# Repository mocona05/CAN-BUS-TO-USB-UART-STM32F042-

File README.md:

# CAN-BUS-TO-USB-UART-STM32F042-
CAN-BUS TO USB-UART(STM32F042)
http://cafe.naver.com/hobbydyi/1781

lcd
http://ko.aliexpress.com/item/1-3-inch-White-OLED-Screen-SH1106-Drive-IC-128-64-I2C-SPI-Parallel-Interface/32299639218.html

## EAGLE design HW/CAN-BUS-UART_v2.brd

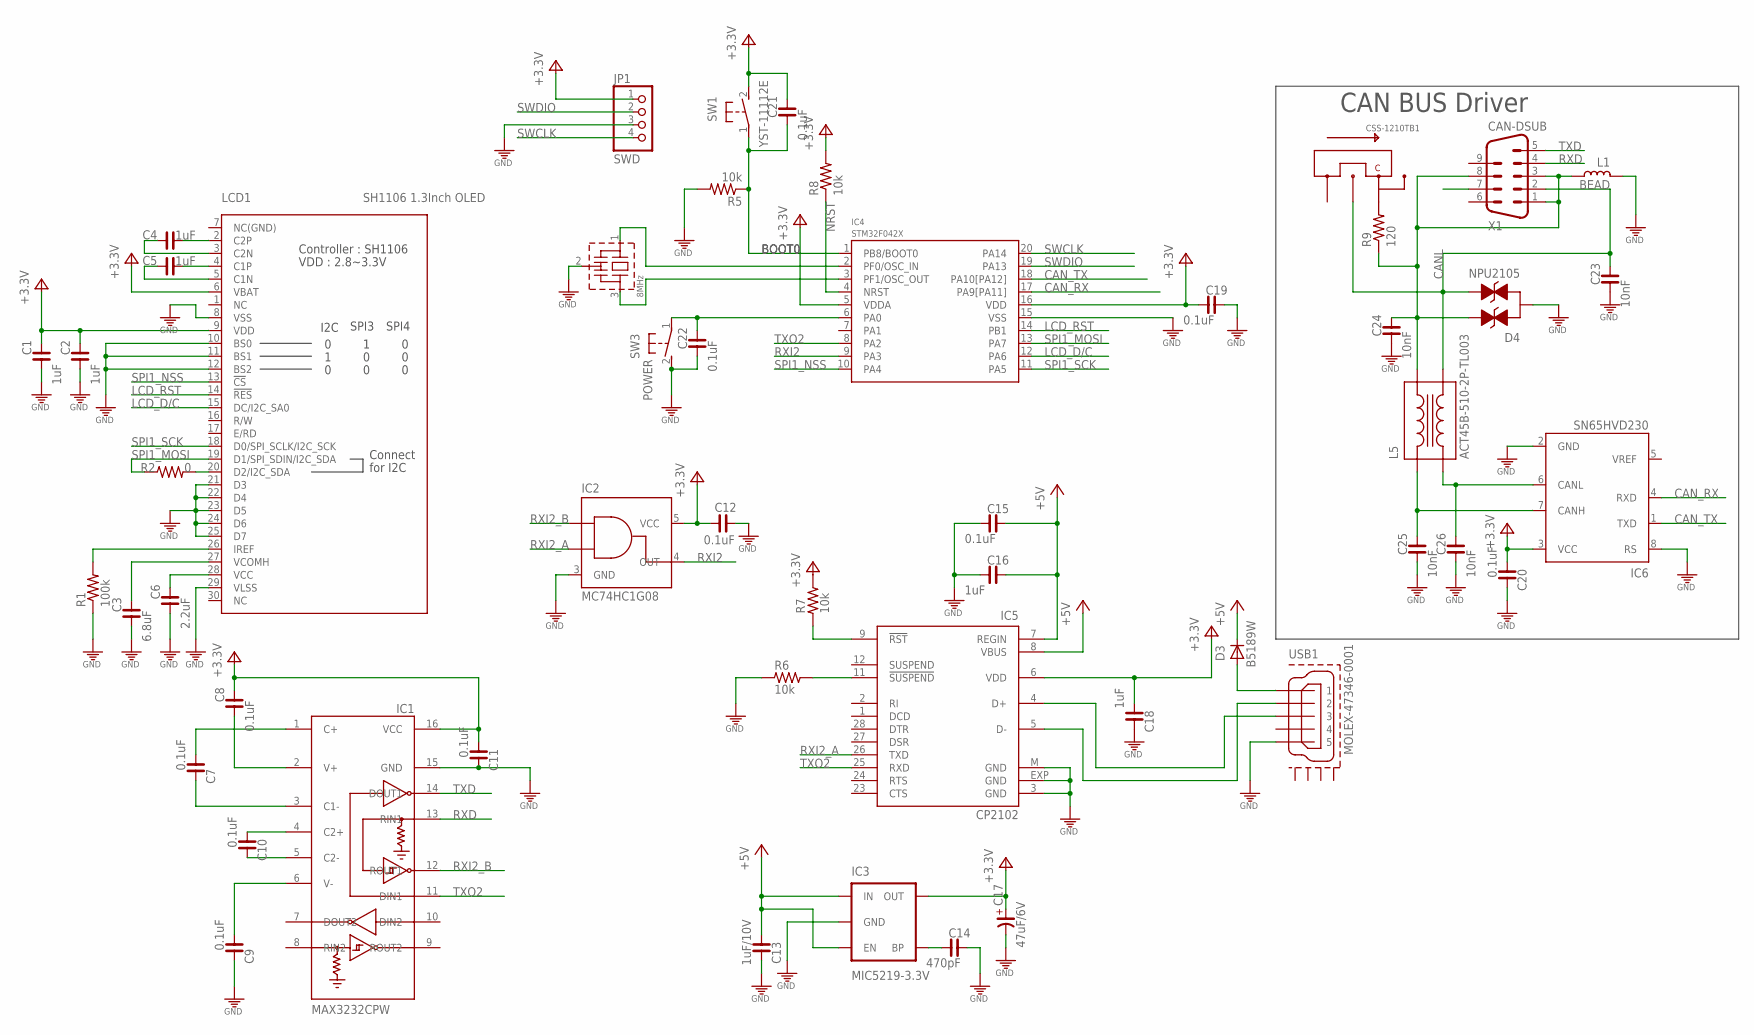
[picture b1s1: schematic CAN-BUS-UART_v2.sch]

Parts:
C1, C2, C4, C5, C16, C18: 1uF; C0603
C3: 6.8uF; C0805
C6: 2.2uF; C0805
C7, C8, C9, C10, C11, C12, C15, C19, C20, C21, C22: 0.1uF; C0603
C13: 1uF/10V; C0603
C14: 470pF; C0603
C17: 47uF/6V; C3528-21/T
C23, C24, C25, C26: 10nF; C0603
D3: B5189W; SOD323
D4: NPU2105; SOT23
IC1: MAX3232CPW; PW_R-PDSO-G16
IC2: MC74HC1G08; SOT23-5L_MC74HC1G08
IC3: MIC5219-3.3V; SOT23-5
IC4: STM32F042X; TSSOP20
IC5: CP2102; MLP28
IC6: SN65HVD230; SO8
JP1: SWD; 1X04M
L1: BEAD; L0805
L5: ACT45B-510-2P-TL003; ACT45B
LCD1: SH1106 1.3Inch OLED; SH1106_1.3OLED_BUTTOM
Q1: 8MHz; CSTLA_X
R1: 100k; R0603@1
R2: 0; R0603@1
R5, R8: 10k; R0603@1
R6, R7: 10k; R0603
R9: 120; R0603@1
SW1: YST-11112E; YST-1112E
SW2: CSS-1210TB1; CSS-1210TB
SW3: POWER; KLT-1105VE
USB1: MOLEX-47346-0001; MOLEX-47364-0001
X1: CAN-DSUB; M09H-1

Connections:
3V3: C1.1, C2.1, C8.1, C11.2, C12.2, C17.+, C18.2, C19.2, C20.2, C21.1, IC1.16 (VCC), IC2.5 (VCC), IC3.5 (OUT), IC4.5 (VDDA), IC4.16 (VDD), IC5.6 (VDD), IC6.3 (VCC), JP1.1, LCD1.6 (VBAT), LCD1.9 (VDD), R7.2, R8.2, SW1.2
+5V: C13.2, C15.1, C16.1, D3.C, IC3.1 (IN), IC3.3 (EN), IC5.7 (REGIN), IC5.8 (VBUS)
BOOT0: C21.2, IC4.1 (PB8/BOOT0), R5.1, SW1.1
CANL: C23.1, D4.S (PIN2), L5.3, SW2.2, X1.2
CAN_RX: IC4.17 (PA9[PA11]), IC6.4 (RXD)
CAN_TX: IC4.18 (PA10[PA12]), IC6.1 (TXD)
GND: C1.2, C2.2, C3.2, C6.2, C9.1, C11.1, C12.1, C13.1, C14.1, C15.2, C16.2, C17.-, C18.1, C19.1, C20.1, C22.2, C23.2, C24.2, C25.2, C26.2, D4.D (PIN3), IC1.15 (GND), IC2.3 (GND), IC3.2 (GND), IC4.15 (VSS), IC5.3 (GND), IC5.EXP (GND), IC5.M (GND), IC6.2 (GND), IC6.8 (RS), JP1.3, L1.2, LCD1.8 (VSS), LCD1.10 (BS0), LCD1.11 (BS1), LCD1.12 (BS2), LCD1.21 (D3), LCD1.22 (D4), LCD1.23 (D5), LCD1.24 (D6), LCD1.25 (D7), LCD1.29 (VLSS), Q1.2 (GND), R1.1, R5.2, R6.1, SW3.2, USB1.5
LCD_D/C: IC4.12 (PA6), LCD1.15 (DC/I2C_SA0)
LCD_RST: IC4.14 (PB1), LCD1.14 (!RES)
unnamed: IC5.9 (!RST), R7.1
unnamed: IC4.2 (PF0/OSC_IN), Q1.1 (IN)
unnamed: IC4.3 (PF1/OSC_OUT), Q1.3 (OUT)
unnamed: D3.A, USB1.1
unnamed: R9.2, SW2.3
unnamed: LCD1.26 (IREF), R1.2
unnamed: C22.1, IC4.6 (PA0), SW3.1
unnamed: IC5.5 (D-), USB1.2
unnamed: C24.1, D4.G (PIN1), L1.1, L5.4, R9.1, X1.1, X1.3, X1.8
unnamed: C14.2, IC3.4 (BP)
unnamed: C26.1, IC6.6 (CANL), L5.2
unnamed: C10.1, IC1.5 (C2-)
unnamed: C4.2, LCD1.2 (C2P)
unnamed: C4.1, LCD1.3 (C2N)
unnamed: C5.2, LCD1.4 (C1P)
unnamed: C5.1, LCD1.5 (C1N)
unnamed: LCD1.20 (D2/I2C_SDA), R2.2
unnamed: IC5.4 (D+), USB1.3
unnamed: C3.1, LCD1.27 (VCOMH)
unnamed: C6.1, LCD1.28 (VCC)
unnamed: IC5.11 (!SUSPEND), R6.2
unnamed: C25.1, IC6.7 (CANH), L5.1
unnamed: C10.2, IC1.4 (C2+)
unnamed: C9.2, IC1.6 (V-)
unnamed: C7.2, IC1.1 (C+)
unnamed: C7.1, IC1.3 (C1-)
unnamed: C8.2, IC1.2 (V+)
NRST: IC4.4 (NRST), R8.1
RXD: IC1.13 (RIN1), X1.4
RXI2: IC2.4 (OUT), IC4.9 (PA3)
RXI2_A: IC2.2 (INA), IC5.26 (TXD)
RXI2_B: IC1.12 (ROUT1), IC2.1 (INB)
SPI1_MOSI: IC4.13 (PA7), LCD1.19 (D1/SPI_SDIN/I2C_SDA), R2.1
SPI1_NSS: IC4.10 (PA4), LCD1.13 (!CS)
SPI1_SCK: IC4.11 (PA5), LCD1.18 (D0/SPI_SCLK/I2C_SCK)
SWCLK: IC4.20 (PA14), JP1.4
SWDIO: IC4.19 (PA13), JP1.2
TXD: IC1.14 (DOUT1), X1.5
TXO2: IC1.11 (DIN1), IC4.8 (PA2), IC5.25 (RXD)

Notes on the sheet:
CAN BUS Driver

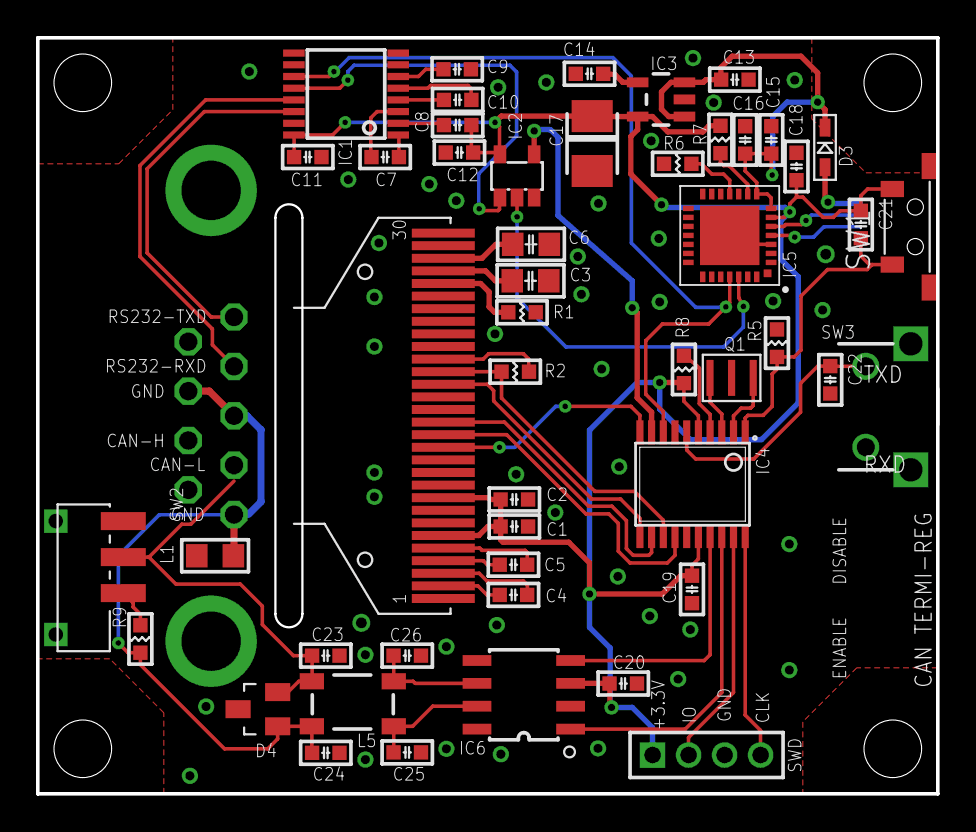
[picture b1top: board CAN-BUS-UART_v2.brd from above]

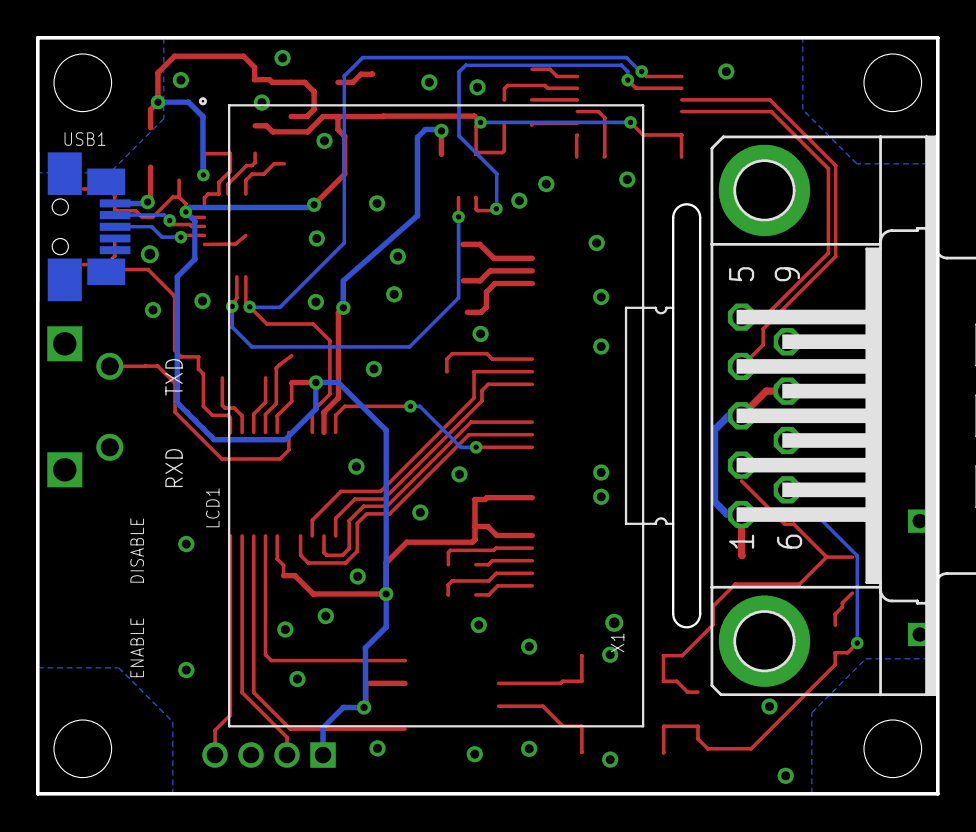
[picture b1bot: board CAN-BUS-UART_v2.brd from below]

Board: 2 copper layers, 50.0 x 42.0 mm, 51 parts (2 on the bottom side), 48 nets.

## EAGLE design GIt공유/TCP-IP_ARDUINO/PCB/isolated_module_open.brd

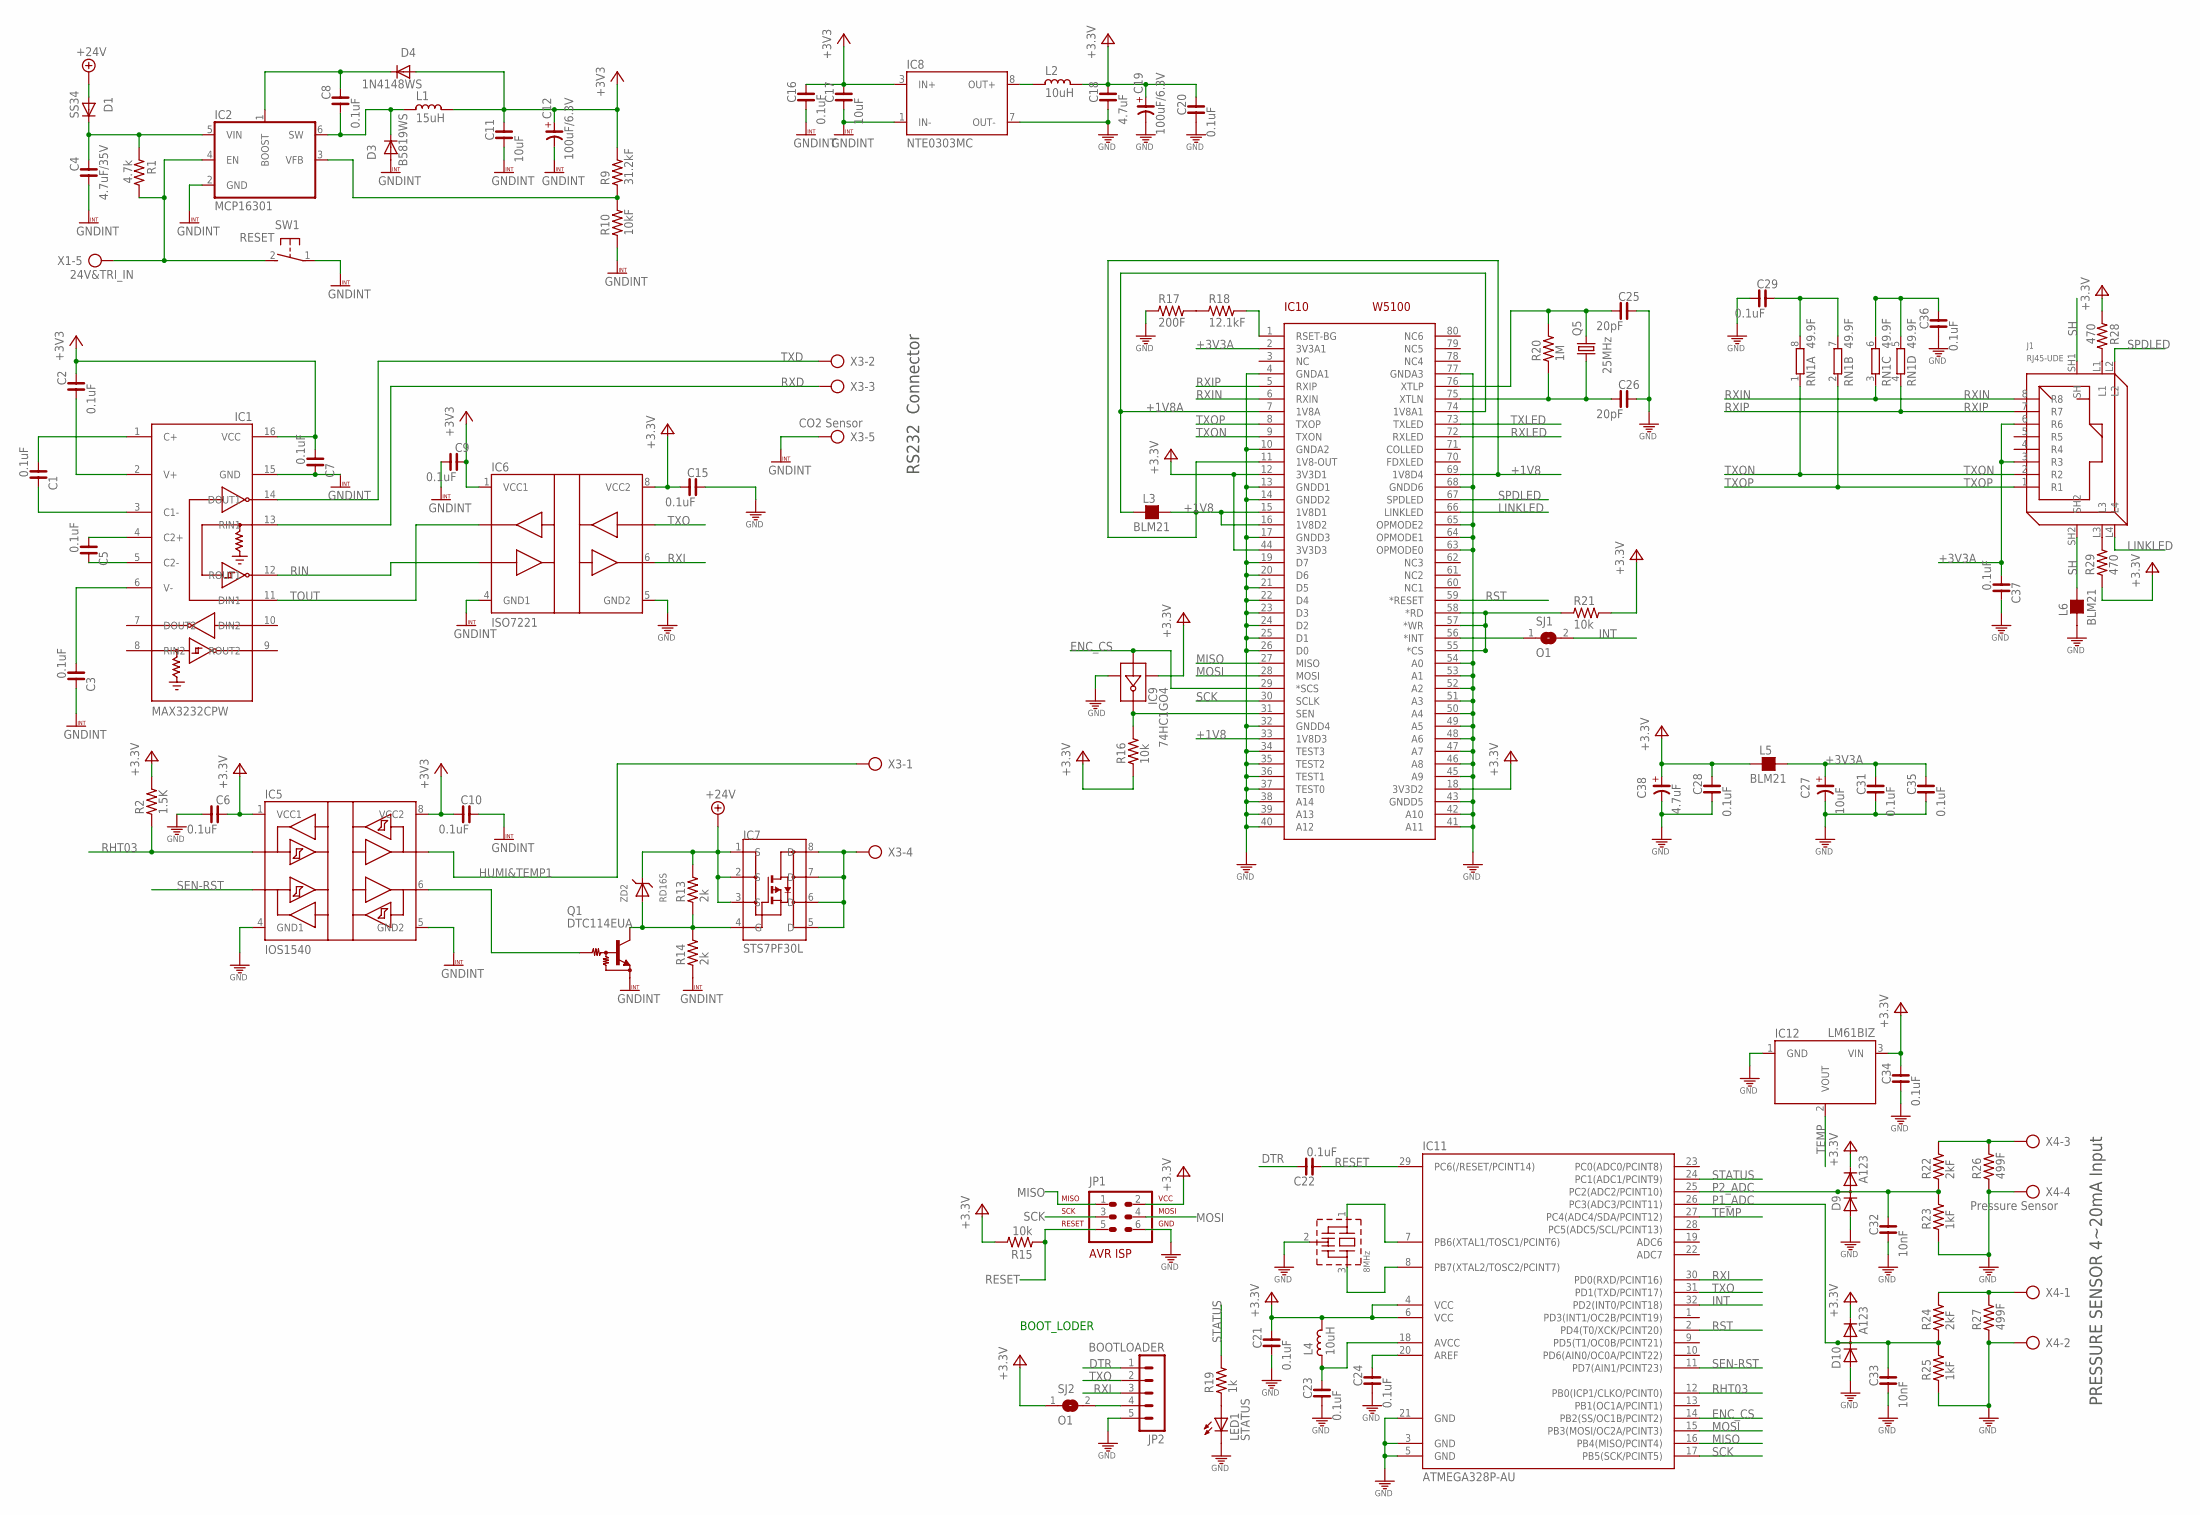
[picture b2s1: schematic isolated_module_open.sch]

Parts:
C1, C2, C3, C5, C6, C7, C8, C9, C10, C15, C16, C20, C21, C22, C23, C24, C28, C29, C31, C34, C35, C36, C37: 0.1uF; C0603
C4: 4.7uF/35V; C3225
C11, C17: 10uF; C0805
C12, C19: 100uF/6.3V; C3528-21/T
C18: 4.7uF; C0805
C25, C26: 20pF; C0603
C27: 10uF; C2012/T
C32, C33: 10nF; C0603
C38: 4.7uF; C2012/T
D1: SS34; DO214AA
D3: B5819WS; SOD323
D4: 1N4148WS; SOD323
D9, D10: A123; SOT23
IC1: MAX3232CPW; PW_R-PDSO-G16
IC2: MCP16301; SOT23-6L
IC5: IOS1540; SO08
IC6: ISO7221; SO8
IC7: STS7PF30L; SO08
IC8: NTE0303MC; NTE0505MC
IC9: 74HC1GO4; SOT753
IC10: W5100; SQFP-S-10X10-80
IC11: ATMEGA328P-AU; TQFP32-08
IC12: LM61BIZ; TO92-
J1: RJ45-UDE; RDA-126B1A1A
JP1: AVR-ISP-6
JP2: BOOTLOADER; MA05-1-IR
L1: 15uH; L4545
L2: 10uH; L4545
L3, L5, L6: BLM21; L0603
L4: 10uH; L0805
LED1: STATUS; LED-1608
Q1: DTC114EUA; SC59-BEC
Q4: 8MHz; CSTLA_X
Q5: 25MHz; SMD5032
R1: 4.7k; R0603
R2: 1.5K; R0603
R9: 31.2kF; R0603
R10: 10kF; R0603
R13, R14: 2k; R0603
R15, R16, R21: 10k; R0603
R17: 200F; R0603
R18: 12.1kF; R0603
R19: 1k; R0603
R20: 1M; R0603
R22, R24: 2kF; R0603
R23, R25: 1kF; R0603
R26, R27: 499F; R0805
R28, R29: 470; R0603
RN1: 49.9F; ARRAY_R3216
SJ1, SJ2: O1; SJ
SW1: RESET; DTSM-3
X1: 24V&TRI_IN; AK500/5
X3: CO2 Sensor; AK500/5
X4: Pressure Sensor; AK500/4
ZD2: RD16S; DSMM

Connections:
3V3: C6.1, C15.2, C18.1, C19.+, C20.1, C21.1, C28.1, C34.1, C38.+, D9.2 (C), D10.2 (C), IC5.1 (VCC1), IC6.8 (VCC2), IC9.5 (VDD), IC10.12 (3V3D1), IC10.18 (3V3D2), IC10.44 (3V3D3), IC11.4 (VCC), IC11.6 (VCC), IC12.3 (VIN), JP1.2, L2.1, L4.1, L5.1, R2.2, R15.2, R16.1, R21.2, R28.1, R29.1, SJ2.1
+1V8: IC10.11 (1V8-OUT), IC10.15 (1V8D1), IC10.16 (1V8D2), IC10.33 (1V8D3), IC10.69 (1V8D4), L3.2
+1V8A: IC10.7 (1V8A), IC10.74 (1V8A1), L3.1
+3V3: C2.1, C7.2, C9.1, C10.2, C11.1, C12.+, C16.1, C17.1, D4.A, IC1.16 (VCC), IC5.8 (VCC2), IC6.1 (VCC1), IC8.3 (IN+), L1.1, R9.2
+3V3A: C27.+, C31.1, C35.1, C37.2, IC10.2 (3V3A1), J1.3 (R3), J1.6 (R6), L5.2
+24V: D1.A, IC7.1 (S), IC7.2 (S), IC7.3 (S), R13.2, ZD2.C
DTR: C22.1, JP2.1
ENC_CS: IC9.2 (A), IC10.29 (*SCS), IC11.14 (PB2(SS/OC1B/PCINT2))
GND: C6.2, C15.1, C18.2, C19.-, C20.2, C21.2, C23.2, C24.2, C25.1, C26.1, C27.-, C28.2, C29.2, C31.2, C32.2, C33.2, C34.2, C35.2, C36.2, C37.1, C38.-, D9.1 (A), D10.1 (A), IC5.4 (GND1), IC6.5 (GND2), IC8.7 (OUT-), IC9.3 (GND), IC10.4 (GNDA1), IC10.10 (GNDA2), IC10.13 (GNDD1), IC10.14 (GNDD2), IC10.17 (GNDD3), IC10.19 (D7), IC10.20 (D6), IC10.21 (D5), IC10.22 (D4), IC10.23 (D3), IC10.24 (D2), IC10.25 (D1), IC10.26 (D0), IC10.32 (GNDD4), IC10.34 (TEST3), IC10.35 (TEST2), IC10.36 (TEST1), IC10.37 (TEST0), IC10.38 (A14), IC10.39 (A13), IC10.40 (A12), IC10.41 (A11), IC10.42 (A10), IC10.43 (GNDD5), IC10.45 (A9), IC10.46 (A8), IC10.47 (A7), IC10.48 (A6), IC10.49 (A5), IC10.50 (A4), IC10.51 (A3), IC10.52 (A2), IC10.53 (A1), IC10.54 (A0), IC10.63 (OPMODE0), IC10.64 (OPMODE1), IC10.65 (OPMODE2), IC10.68 (GNDD6), IC10.77 (GNDA3), IC11.3 (GND), IC11.5 (GND), IC11.21 (GND), IC12.1 (GND), JP1.6, JP2.5, L6.1, LED1.C, Q4.2 (GND), R17.1, R23.1, R25.1, R26.1, R27.1, X4.2, X4.4
GNDINT: C3.1, C4.2, C7.1, C9.2, C10.1, C11.2, C12.-, C16.2, C17.2, D3.A, IC1.15 (GND), IC2.2 (GND), IC5.5 (GND2), IC6.4 (GND1), IC8.1 (IN-), Q1.1 (GND), R10.1, R14.1, SW1.1, X3.5
HUMI&TEMP1: IC5.7 (SDA2), X3.1
INT: IC11.32 (PD2(INT0/PCINT18)), SJ1.2
LINKLED: IC10.66 (LINKLED), J1.L4
MISO: IC10.27 (MISO), IC11.16 (PB4(MISO/PCINT4)), JP1.1
MOSI: IC10.28 (MOSI), IC11.15 (PB3(MOSI/OC2A/PCINT3)), JP1.4
unnamed: C5.1, IC1.5 (C2-)
unnamed: IC11.7 (PB6(XTAL1/TOSC1/PCINT6)), Q4.1 (IN)
unnamed: IC11.8 (PB7(XTAL2/TOSC2/PCINT7)), Q4.3 (OUT)
unnamed: C5.2, IC1.4 (C2+)
unnamed: C3.2, IC1.6 (V-)
unnamed: C2.2, IC1.2 (V+)
unnamed: C1.2, IC1.1 (C+)
unnamed: C1.1, IC1.3 (C1-)
unnamed: R22.2, R26.2, X4.3
unnamed: C4.1, D1.C, IC2.5 (VIN), R1.1
unnamed: LED1.A, R19.1
unnamed: IC10.55 (*CS), IC10.57 (*WR), IC10.58 (*RD), R21.1
unnamed: R17.2, R18.1
unnamed: J1.L3, R29.2
unnamed: J1.L1, R28.2
unnamed: C36.1, RN1.5 (2), RN1.6 (2)
unnamed: IC10.56 (*INT), SJ1.1
unnamed: C29.1, RN1.7 (2), RN1.8 (2)
unnamed: IC10.1 (RSET-BG), R18.2
unnamed: IC8.8 (OUT+), L2.2
unnamed: C8.2, D3.C, IC2.6 (SW), L1.2
unnamed: IC2.3 (VFB), R9.1, R10.2
unnamed: C8.1, D4.C, IC2.1 (BOOST)
unnamed: IC2.4 (EN), R1.2, SW1.2, X1.5
unnamed: R24.2, R27.2, X4.1
unnamed: C24.1, IC11.20 (AREF)
unnamed: C23.1, IC11.18 (AVCC), L4.2
unnamed: IC7.5 (D), IC7.6 (D), IC7.7 (D), IC7.8 (D), X3.4
unnamed: IC5.6 (SCL2), Q1.2 (IN)
unnamed: C25.2, IC10.76 (XTLP), Q5.3 (2), R20.2
unnamed: IC7.4 (G), Q1.3 (OUT), R13.1, R14.2, ZD2.A
unnamed: IC9.4 (Y), IC10.31 (SEN), R16.2
unnamed: JP2.4, SJ2.2
unnamed: C26.2, IC10.75 (XTLN), Q5.1, R20.1
P1_ADC: C33.1, D10.3 (AC), IC11.26 (PC3(ADC3/PCINT11)), R24.1, R25.2
P2_ADC: C32.1, D9.3 (AC), IC11.25 (PC2(ADC2/PCINT10)), R22.1, R23.2
RESET: C22.2, IC11.29 (PC6(/RESET/PCINT14)), JP1.5, R15.1
RHT03: IC5.2 (SDA1), IC11.12 (PB0(ICP1/CLKO/PCINT0)), R2.1
RIN: IC1.12 (ROUT1), IC6.3 (INB)
RST: IC10.59 (*RESET), IC11.2 (PD4(T0/XCK/PCINT20))
RXD: IC1.13 (RIN1), X3.3
RXI: IC6.6 (OUTB), IC11.30 (PD0(RXD/PCINT16)), JP2.3
RXIN: IC10.6 (RXIN), J1.8 (R8), RN1.3 (1)
RXIP: IC10.5 (RXIP), J1.7 (R7), RN1.4 (1)
RXLED: IC10.72 (RXLED)
SCK: IC10.30 (SCLK), IC11.17 (PB5(SCK/PCINT5)), JP1.3
SEN-RST: IC5.3 (SCL1), IC11.11 (PD7(AIN1/PCINT23))
SH: J1.SH1 (SH), J1.SH2, L6.2
SPDLED: IC10.67 (SPDLED), J1.L2
STATUS: IC11.24 (PC1(ADC1/PCINT9)), R19.2
TEMP: IC11.27 (PC4(ADC4/SDA/PCINT12)), IC12.2 (VOUT)
TOUT: IC1.11 (DIN1), IC6.2 (OUTA)
TXD: IC1.14 (DOUT1), X3.2
TXLED: IC10.73 (TXLED)
TXO: IC6.7 (INA), IC11.31 (PD1(TXD/PCINT17)), JP2.2
TXON: IC10.9 (TXON), J1.2 (R2), RN1.1
TXOP: IC10.8 (TXOP), J1.1 (R1), RN1.2 (1)

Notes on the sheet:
BOOT_LODER
RS232 Connector
PRESSURE SENSOR 4~20mA Input

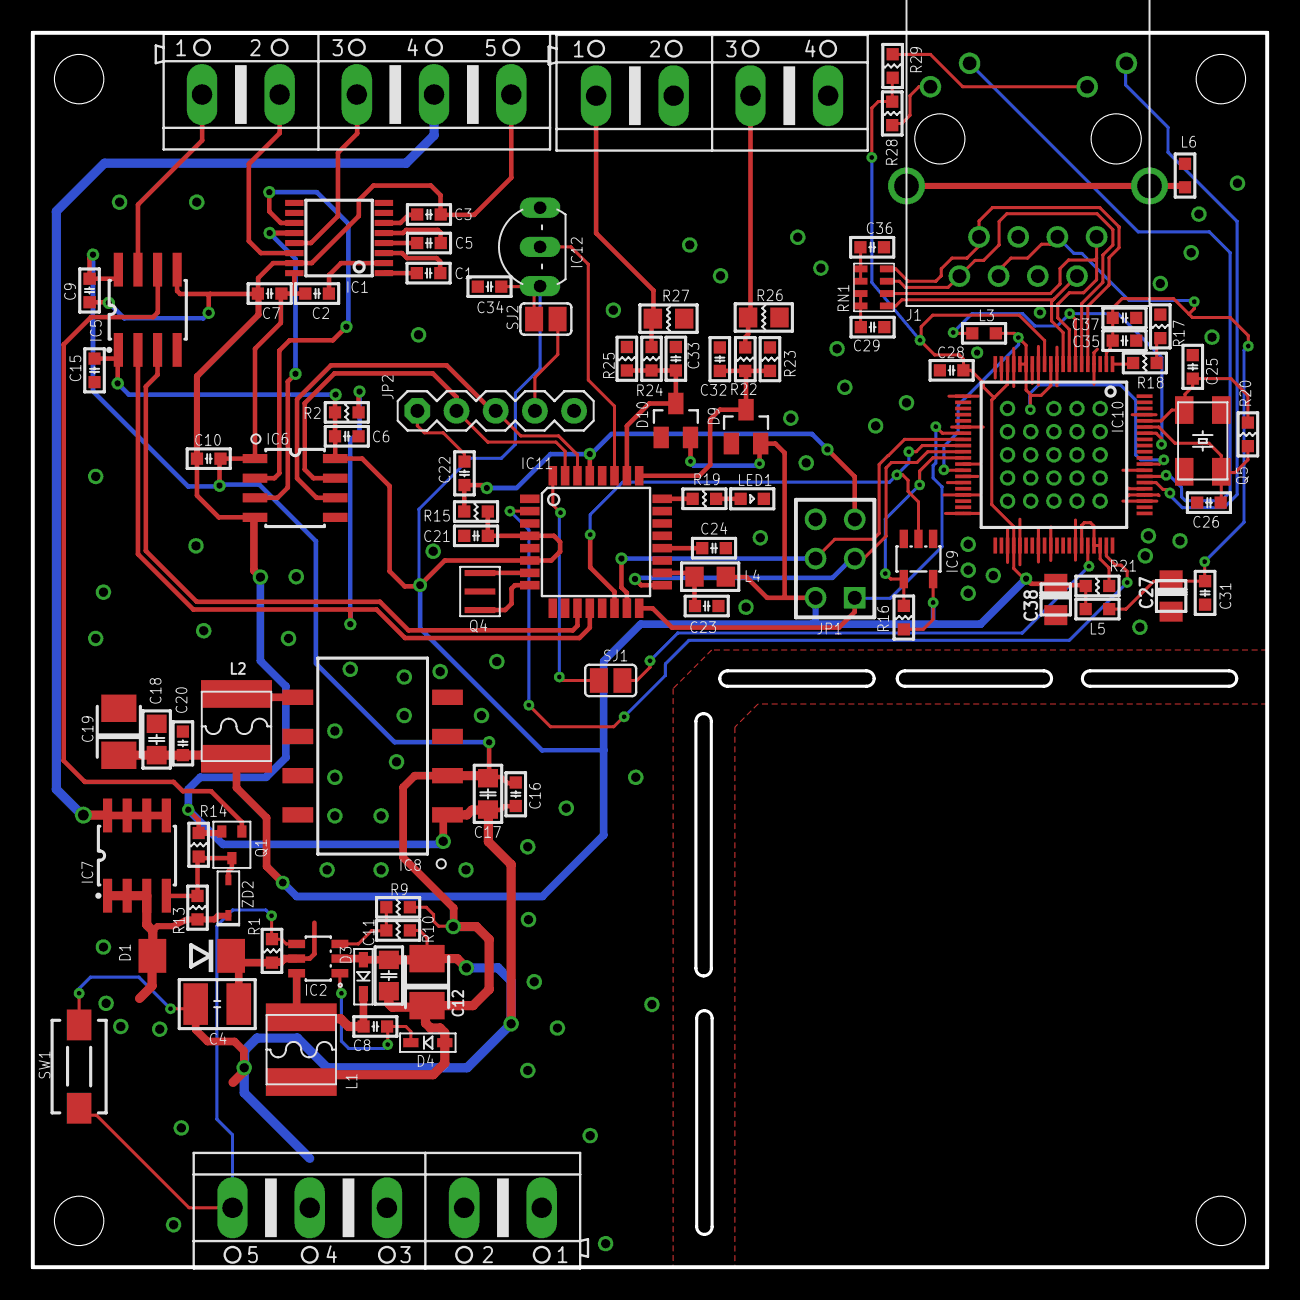
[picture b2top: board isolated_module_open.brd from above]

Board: 2 copper layers, 80.0 x 80.0 mm, 92 parts (0 on the bottom side), 70 nets.

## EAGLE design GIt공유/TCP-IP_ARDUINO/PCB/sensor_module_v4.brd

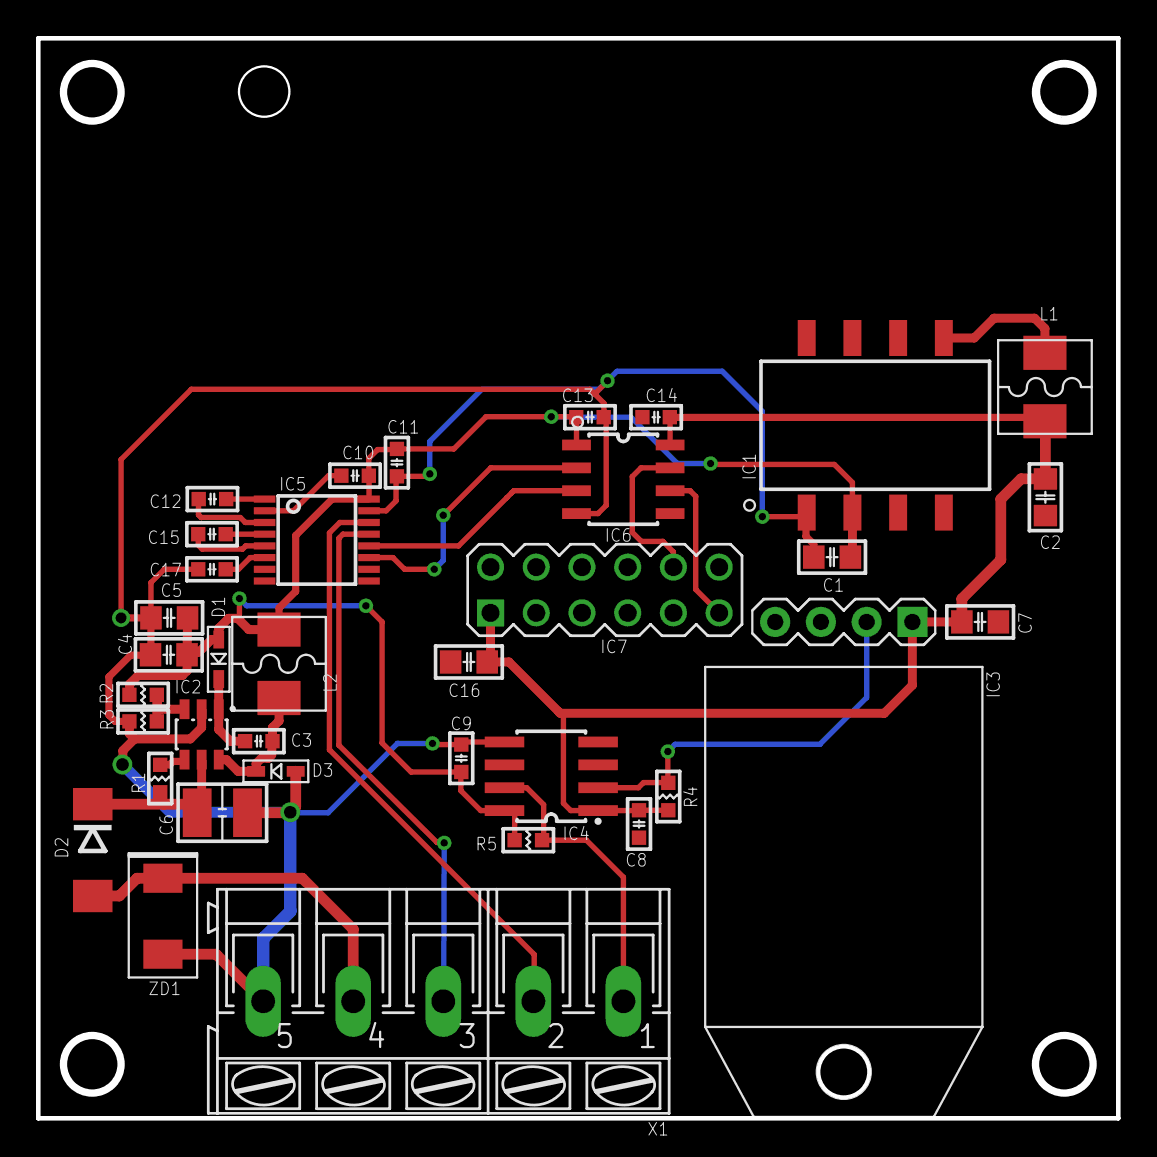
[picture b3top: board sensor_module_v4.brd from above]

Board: 2 copper layers, 60.0 x 60.0 mm, 36 parts (0 on the bottom side), 25 nets.

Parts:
C1, C4, C5, C7, C16: 10uF; C0805
C2: 4.7uF; C0805
C3, C8, C9, C10, C11, C12, C13, C14, C15, C17: 0.1uF; C0603
C6: 10uF/35V; C3225
D1: 1N4148WS; SOD323
D2: SS34; DO214AA
D3: B5819WS; SOD323
IC1: NTE0505MC
IC2: MCP16301; SOT23-6L
IC3: RHT03; RHT03-FRONT
IC4: IOS1540; SO08
IC5: MAX3232CPW; PW_R-PDSO-G16
IC6: ISO7221; SO8
IC7: T6615; T63172
L1: 47uH; L5845
L2: 22uH; L5845
R1: 10M; R0603
R2: 52.3kF; R0603
R3: 10kF; R0603
R4, R5: 1.5K; R0603
X1: AK300/5
ZD1: SM6T33CAY; SMB

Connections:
+5V: C1.1, C4.1, C5.1, C9.2, C10.1, C11.2, C13.1, D1.A, IC1.3, IC4.8, IC5.16, IC6.1, L2.1, R2.2, R5.2
+5V/1: C2.1, C7.1, C8.1, C14.2, C16.1, IC3.1, IC4.1, IC6.8, IC7.1, L1.1, R4.2
+24V: D2.A, X1.4, ZD1.C
GND: C2.2, C7.2, C8.2, C14.1, C16.2, IC1.7, IC3.4, IC4.4, IC6.5, IC7.2, IC7.3, IC7.12
GNDINT: C1.2, C4.2, C5.2, C6.2, C9.1, C11.1, C13.2, C17.1, D3.A, IC1.1, IC2.2, IC4.5, IC5.15, IC6.4, R3.1, X1.5, ZD1.A
HUMI&TEMP: IC4.7, R5.1, X1.1
unnamed: IC6.6, IC7.11
unnamed: IC6.7, IC7.10
unnamed: C6.1, D2.C, IC2.5, R1.1
unnamed: C15.1, IC5.5
unnamed: C15.2, IC5.4
unnamed: C17.2, IC5.6
unnamed: C10.2, IC5.2
unnamed: C12.2, IC5.1
unnamed: C12.1, IC5.3
unnamed: IC1.8, L1.2
unnamed: C3.2, D3.C, IC2.6, L2.2
unnamed: IC2.3, R2.1, R3.2
unnamed: C3.1, D1.C, IC2.1
unnamed: IC2.4, R1.2
RHT03: IC3.2, IC4.2, R4.1
RIN: IC5.12, IC6.3
RXD: IC5.13, X1.3
TOUT: IC5.11, IC6.2
TXD: IC5.14, X1.2

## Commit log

2016-04-29 ALPHA VERSION
2016-04-29 아두이노 소스 폴더변경
2016-04-29 이미지추가
2016-04-30 image add
